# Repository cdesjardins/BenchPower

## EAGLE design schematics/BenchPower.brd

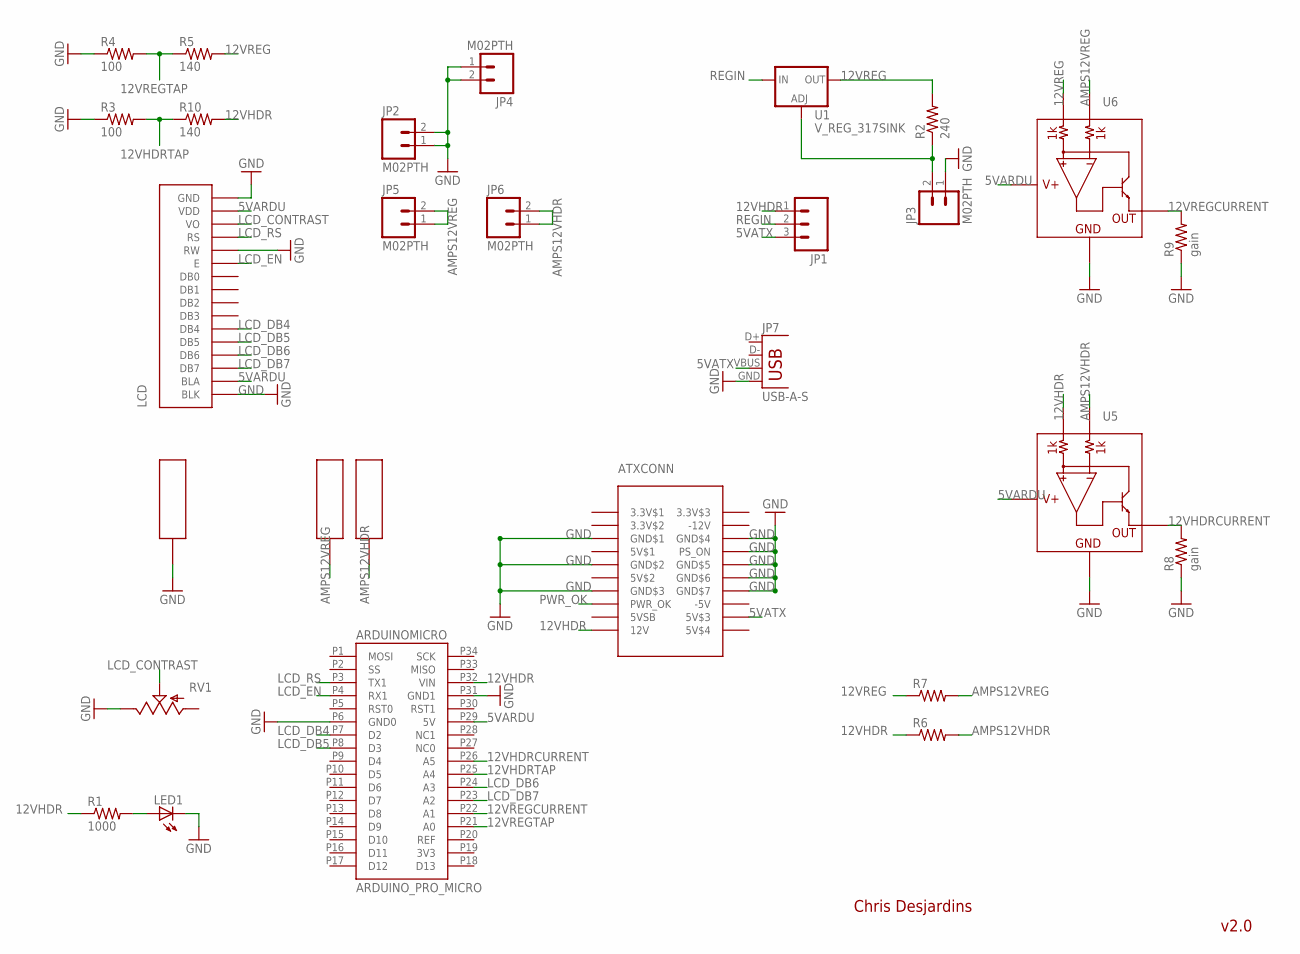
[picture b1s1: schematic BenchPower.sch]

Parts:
ARDUINOMICRO: ARDUINO_PRO_MICRO
ATXCONN: ATXPOWER
JP1: M03PTH; 1X03
JP2, JP3, JP4, JP5, JP6: M02PTH; 1X02
JP7: USB-A-S
LCD: 16X2LCDDT162C; DT162C
LED1: LED3MM
PWR1, PWR2: BINDINGPOST
R1: 1000; AXIAL-0.3
R2: 240; AXIAL-0.3
R3, R4: 100; AXIAL-0.3
R5, R10: 140; AXIAL-0.3
R6, R7: RESISTOR1206; 1206
R8, R9: gain; AXIAL-0.3
RV1: POT3266; 3266W
U1: V_REG_317SINK; TO220-ADJ
U5, U6: INA139; SOT23-5
U$5: BINDINGPOST

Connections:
3.3V$1: ATXCONN.P$1 (3.3V$1)
3.3V$2: ATXCONN.P$2 (3.3V$2)
3.3V$3: ATXCONN.P$11 (3.3V$3)
3V3: ARDUINOMICRO.P19 (3V3)
5V$1: ATXCONN.P$4 (5V$1)
5V$2: ATXCONN.P$6 (5V$2)
5V$4: ATXCONN.P$20 (5V$4)
5VARDU: ARDUINOMICRO.P29 (5V), LCD.P$2 (VDD), LCD.P$15 (BLA), U5.5 (V+), U6.5 (V+)
5VATX: ATXCONN.P$19 (5V$3), JP1.3, JP7.VBUS
5VSB: ATXCONN.P$9 (5VSB)
12VHDR: ARDUINOMICRO.P32 (VIN), ATXCONN.P$10 (12V), JP1.1, R1.P$1 (1), R6.1, R10.P$2 (2), U5.3 (VIN+)
12VHDRCURRENT: ARDUINOMICRO.P26 (A5), R8.P$2 (2), U5.1 (OUT)
12VHDRTAP: ARDUINOMICRO.P25 (A4), R3.P$2 (2), R10.P$1 (1)
12VREG: R2.P$2 (2), R5.P$2 (2), R7.1, U1.OUT, U6.3 (VIN+)
12VREGCURRENT: ARDUINOMICRO.P22 (A1), R9.P$2 (2), U6.1 (OUT)
12VREGTAP: ARDUINOMICRO.P21 (A0), R4.P$2 (2), R5.P$1 (1)
-5V: ATXCONN.P$18 (-5V)
-12V: ATXCONN.P$12 (-12V)
ADJREG1: JP3.2, R2.P$1 (1), U1.ADJ
AMPS12VHDR: JP6.1, JP6.2, PWR2.P$1, R6.2, U5.4 (VIN-)
AMPS12VREG: JP5.1, JP5.2, PWR1.P$1, R7.2, U6.4 (VIN-)
GND: ARDUINOMICRO.P6 (GND0), ARDUINOMICRO.P31 (GND1), ATXCONN.P$3 (GND$1), ATXCONN.P$5 (GND$2), ATXCONN.P$7 (GND$3), ATXCONN.P$13 (GND$4), ATXCONN.P$14 (PS_ON), ATXCONN.P$15 (GND$5), ATXCONN.P$16 (GND$6), ATXCONN.P$17 (GND$7), JP2.1, JP2.2, JP3.1, JP4.1, JP4.2, JP7.GND, LCD.P$1 (GND), LCD.P$5 (RW), LCD.P$16 (BLK), LED1.K (C), R3.P$1 (1), R4.P$1 (1), R8.P$1 (1), R9.P$1 (1), RV1.P$1 (E), U5.2 (GND), U6.2 (GND), U$5.P$1
LCD_CONTRAST: LCD.P$3 (VO), RV1.P$2 (S)
LCD_DB4: ARDUINOMICRO.P7 (D2), LCD.P$11 (DB4)
LCD_DB5: ARDUINOMICRO.P8 (D3), LCD.P$12 (DB5)
LCD_DB6: ARDUINOMICRO.P24 (A3), LCD.P$13 (DB6)
LCD_DB7: ARDUINOMICRO.P23 (A2), LCD.P$14 (DB7)
LCD_EN: ARDUINOMICRO.P4 (RX1), LCD.P$6 (E)
LCD_RS: ARDUINOMICRO.P3 (TX1), LCD.P$4 (RS)
unnamed: LED1.A, R1.P$2 (2)
PWR_OK: ATXCONN.P$8 (PWR_OK)
REF: ARDUINOMICRO.P20 (REF)
REGIN: JP1.2, U1.IN

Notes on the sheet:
Chris Desjardins
v2.0

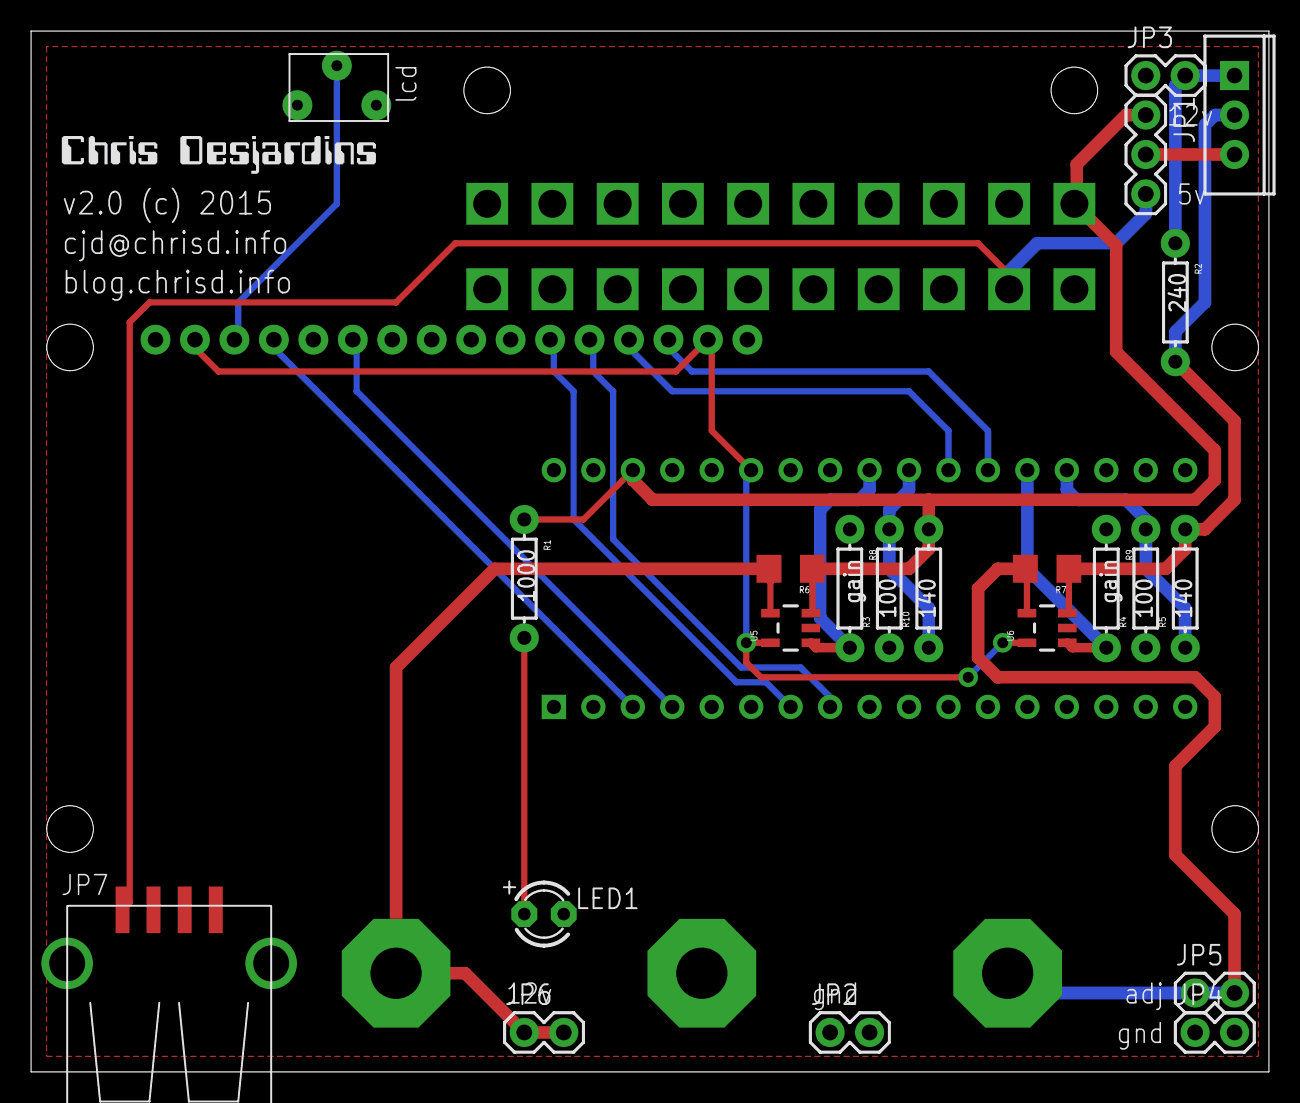
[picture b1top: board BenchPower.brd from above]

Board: 2 copper layers, 79.7 x 67.0 mm, 29 parts (0 on the bottom side), 21 nets.

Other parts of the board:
U$3: LOGO

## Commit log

2014-04-09 Adding new board to git
2014-04-16 Updates to bench power
2014-04-19 Use new op amp
2014-04-19 Small routing changes
2014-04-22 Rework opamp layout
2014-04-22 Route signals
2014-04-23 Simplify
2014-04-24 Final pass
2014-05-05 Adding readme
2014-05-09 Updates for rev 2
2014-05-10 Add code, and update to rev to of hardware
2014-05-10 Adding updates for v2.0 and source code for arduino
2014-05-11 Adjust voltage sense software
2014-07-26 Small routing change for trimpot
2014-10-29 Update image for new layout
2014-12-13 Adding new headers for jumper wires
2015-11-15 Move pot off board, and other updates for v2.0
2015-11-15 Flip the lm317 for heat sinking to the supply case
2015-11-15 Reroute a bunch of stuff for symmetry
2015-11-15 Reroute the lcd
2015-11-15 Move some text
2015-11-16 Small reroute for extra space
2015-11-16 New layout
2015-11-16 Rearrange graphics
2015-11-16 Reroute a line
2015-11-16 Reroute another line
2015-11-17 Make 12v or 5v selectable into regulator
2015-11-17 Move 2k pot header

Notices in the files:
schematics/BenchPower.brd:
v2.0 (c) 2015
parts and their libraries:
SparkFun-PowerIC: Licensing: Creative Commons ShareAlike 4.0 International - https://creativecommons.org/licenses/by-sa/4.0
